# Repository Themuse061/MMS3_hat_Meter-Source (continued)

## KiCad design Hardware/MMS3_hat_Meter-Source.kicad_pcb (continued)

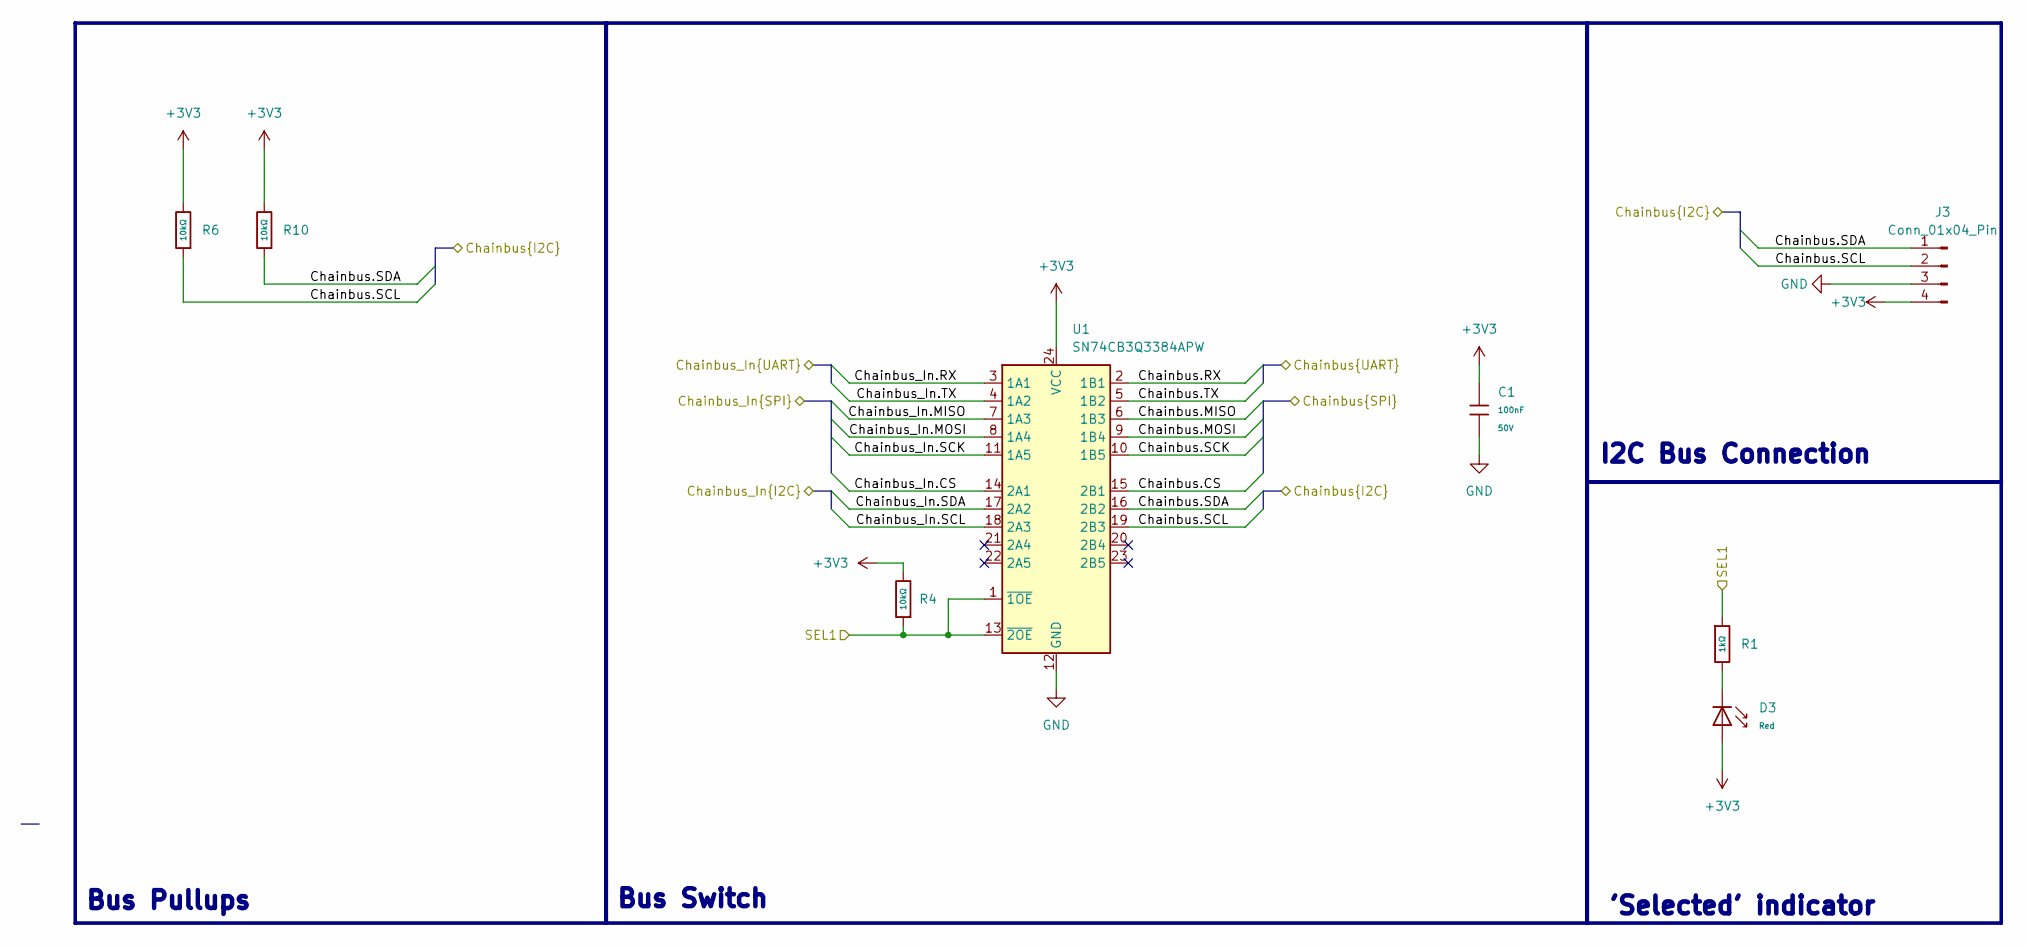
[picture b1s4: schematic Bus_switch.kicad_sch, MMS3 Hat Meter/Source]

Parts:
C1: 100nF; C_0603; Voltage Rated 50V; Tolerance ±10%; Part CC0603KRX7R9BB104; LCSC C14663
D3: Red; D_0603; Part KT-0603R; LCSC C2286
J3: Conn_01x04_Pin; PinHeader_1x04_P2.54mm_Vertical
R1: 1kΩ; R_0603; Overload Voltage (Max) 75V; Tolerance ±1%; Part 0603WAF1001T5E; LCSC C21190
R4, R6, R10: 10kΩ; R_0603; Overload Voltage (Max) 75V; Tolerance ±1%; Part 0603WAF1002T5E; LCSC C25804
U1: SN74CB3Q3384APW; TSSOP-24_4.4x7.8mm_P0.65mm; LCSC C469874

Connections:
+3V3: C1.1, D3.2, J3.4, R4.2, R6.2, R10.2, U1.24 (VCC); also elsewhere on the board
/Bus_switch/Chainbus.CS: U1.15 (2B1)
/Bus_switch/Chainbus.MISO: U1.6 (1B3)
/Bus_switch/Chainbus.MOSI: U1.9 (1B4)
/Bus_switch/Chainbus.RX: U1.2 (1B1)
/Bus_switch/Chainbus.SCK: U1.10 (1B5)
/Bus_switch/Chainbus.SCL: J3.2, R6.1, U1.19 (2B3); also elsewhere on the board
/Bus_switch/Chainbus.SDA: J3.1, R10.1, U1.16 (2B2); also elsewhere on the board
/Bus_switch/Chainbus.TX: U1.5 (1B2)
/Bus_switch/Chainbus_In.CS: U1.14 (2A1)
/Bus_switch/Chainbus_In.MISO: U1.7 (1A3)
/Bus_switch/Chainbus_In.MOSI: U1.8 (1A4)
/Bus_switch/Chainbus_In.RX: U1.3 (1A1)
/Bus_switch/Chainbus_In.SCK: U1.11 (1A5)
/Bus_switch/Chainbus_In.SCL: U1.18 (2A3); also elsewhere on the board
/Bus_switch/Chainbus_In.SDA: U1.17 (2A2); also elsewhere on the board
/Bus_switch/Chainbus_In.TX: U1.4 (1A2)
/Bus_switch/SEL1: R1.1, R4.1, U1.1 (~1OE), U1.13 (~2OE); also elsewhere on the board
GND: C1.2, J3.3, U1.12 (GND); also elsewhere on the board
unnamed: D3.1, R1.2

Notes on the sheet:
Bus Switch
'Selected' indicator
Bus Pullups
I2C Bus Connection

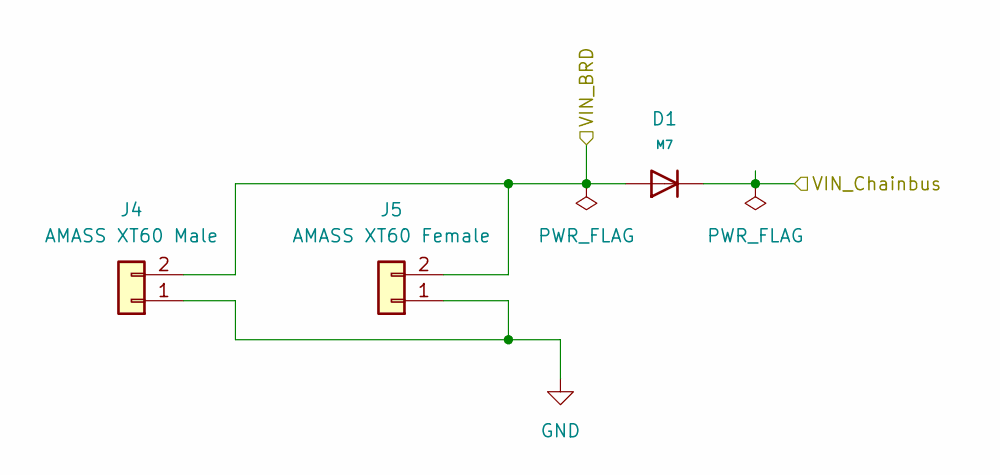
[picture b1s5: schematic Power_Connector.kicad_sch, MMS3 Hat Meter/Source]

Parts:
D1: M7; D_SMA; Forward Voltage (Vf@If) 1.1V@1A; Reverse Voltage (Vr) 1kV; Part M7; LCSC C95872
J4: AMASS XT60 Male; AMASS_XT60PW-M_1x02_P7.20mm_Horizontal; LCSC C98732
J5: AMASS XT60 Female; AMASS_XT60PW-F_1x02_P7.20mm_Horizontal; LCSC C428722

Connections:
/Power Connector/VIN_Chainbus: D1.1
GND: J4.1, J5.1; also elsewhere on the board
VIN_CHAINBUS: D1.2, J4.2, J5.2; also elsewhere on the board

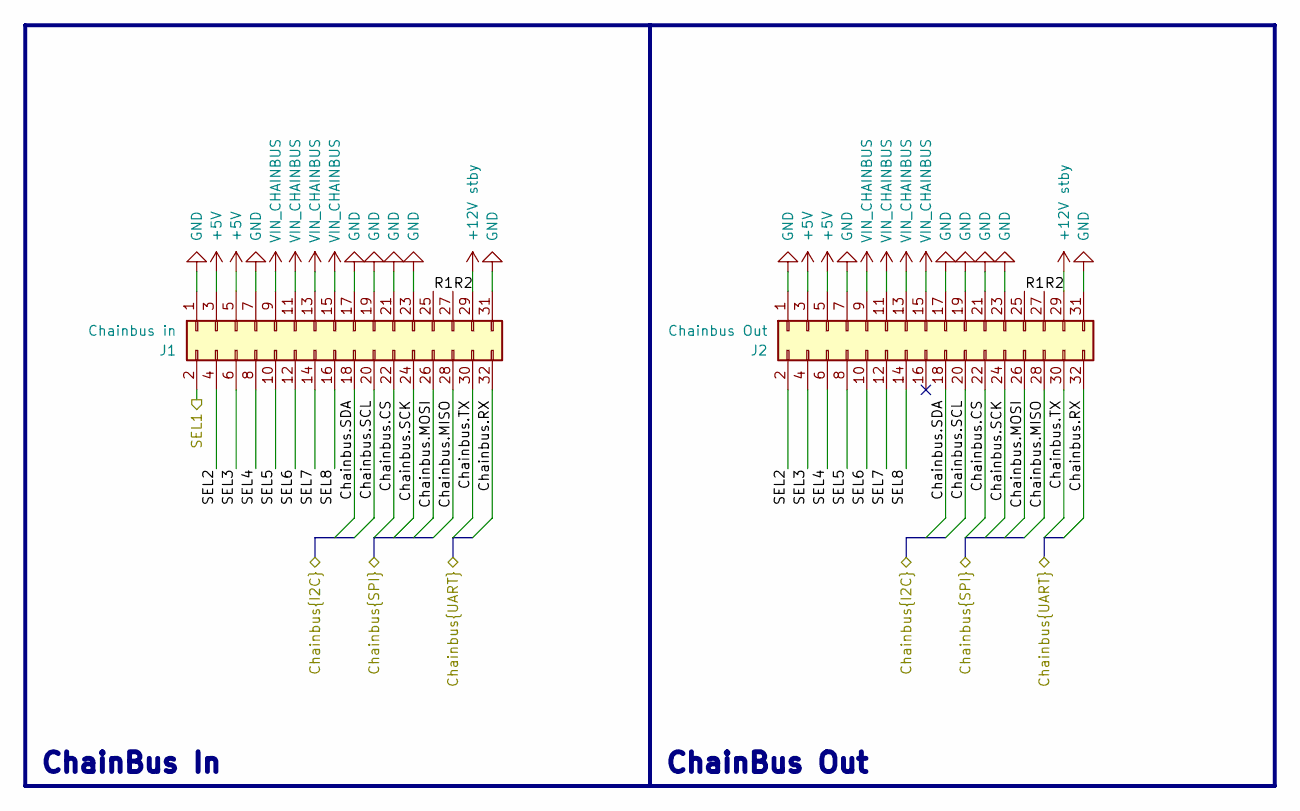
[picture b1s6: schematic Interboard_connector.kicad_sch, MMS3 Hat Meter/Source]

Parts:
J1: Chainbus in; PinHeader_2x16_P2.54mm_Vertical_SMD
J2: Chainbus Out; PinSocket_2x16_P2.54mm_Vertical_SMD

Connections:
+5V: J1.3, J1.5, J2.3, J2.5; also elsewhere on the board
+12V stby: J1.29, J2.29
/Bus_switch/Chainbus_In.SCL: J1.20, J2.20; also elsewhere on the board
/Bus_switch/Chainbus_In.SDA: J1.18, J2.18; also elsewhere on the board
/Bus_switch/SEL1: J1.2; also elsewhere on the board
/Interboard_connector/Chainbus.CS: J1.22, J2.22
/Interboard_connector/Chainbus.MISO: J1.28, J2.28
/Interboard_connector/Chainbus.MOSI: J1.26, J2.26
/Interboard_connector/Chainbus.RX: J1.32, J2.32
/Interboard_connector/Chainbus.SCK: J1.24, J2.24
/Interboard_connector/Chainbus.TX: J1.30, J2.30
/Interboard_connector/R1: J1.25, J2.25
/Interboard_connector/R2: J1.27, J2.27
/Interboard_connector/SEL2: J1.4, J2.2
/Interboard_connector/SEL3: J1.6, J2.4
/Interboard_connector/SEL4: J1.8, J2.6
/Interboard_connector/SEL5: J1.10, J2.8
/Interboard_connector/SEL6: J1.12, J2.10
/Interboard_connector/SEL7: J1.14, J2.12
/Interboard_connector/SEL8: J1.16, J2.14
GND: J1.1, J1.7, J1.17, J1.19, J1.21, J1.23, J1.31, J2.1, J2.7, J2.17, J2.19, J2.21, J2.23, J2.31; also elsewhere on the board
VIN_CHAINBUS: J1.9, J1.11, J1.13, J1.15, J2.9, J2.11, J2.13, J2.15; also elsewhere on the board

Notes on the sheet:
ChainBus In
ChainBus Out

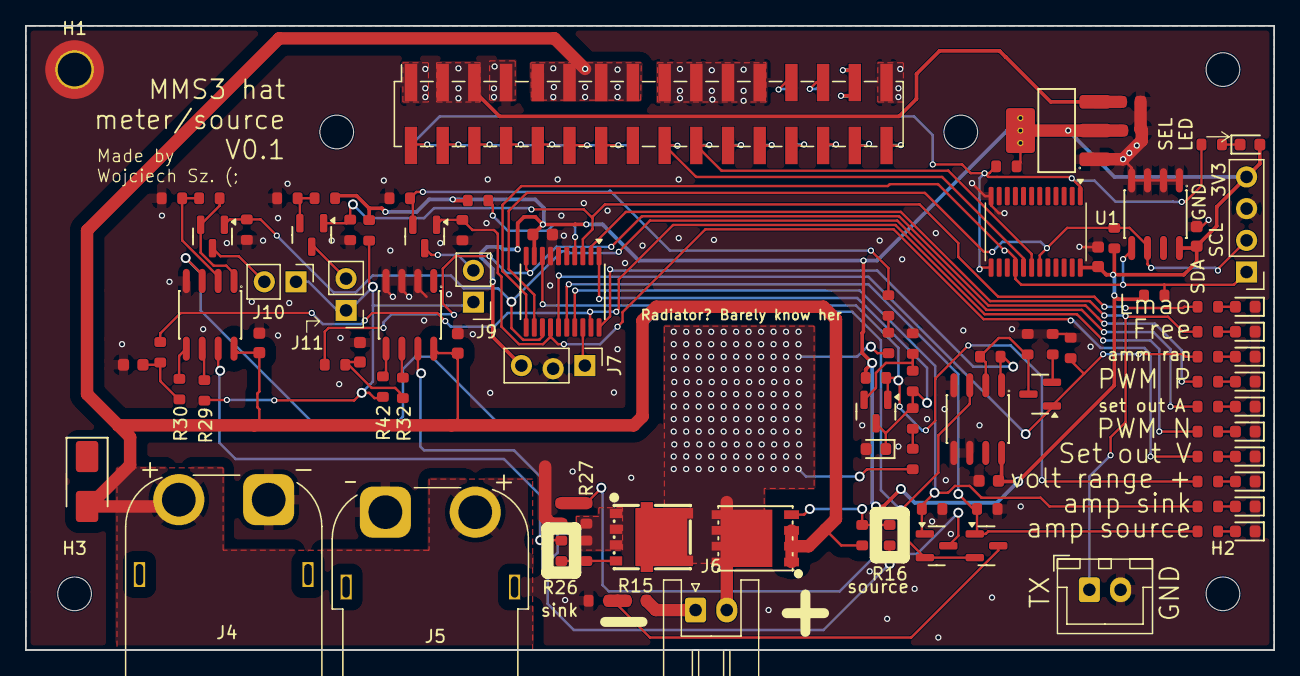
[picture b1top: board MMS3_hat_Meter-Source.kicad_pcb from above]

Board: 2 copper layers, 100.0 x 50.0 mm, 107 parts (1 on the bottom side), 79 nets.
